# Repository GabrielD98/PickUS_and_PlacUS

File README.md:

# PickUS and PlacUS

A 4-axis (X, Y, Z, Yaw) PCB pick-and-place machine for automated SMD component assembly. Built for the S4 robotics project at Université de Sherbrooke.

## Table of Contents

1. [About](#about)
2. [Features](#features)
3. [Tech Stack](#tech-stack)
4. [Project Structure](#project-structure)
5. [Quick Start](#quick-start)
6. [Roadmap](#roadmap)
7. [Contributing](#contributing)
8. [License](#license)
9. [Contact](#contact)

---

## About

### Problem
Manual SMD component placement onto PCBs is time-consuming and error-prone. Small labs and educational institutions need an affordable pick-and-place machine for fast prototyping.

### Solution
PickUS and PlacUS is an open-source, 4-axis automated pick-and-place machine that:
- Picks SMD components using a vacuum pump system
- Places them onto PCBs with positional accuracy
- Uses stepper motors for precise X, Y, Z, and rotational (Yaw) control
- Integrates with KiCad placement files for automated workflows

### Audience
Ideal for robotics project teams, PCB assembly labs, and makers who need to automate component placement without high capital investment.

---

## Features

- **4-Axis Control**: X, Y, Z positioning + Yaw rotation for flexible placement
- **Vacuum Pick System**: Pneumatic pump and valve for reliable component pickup
- **Pressure Sensing**: Real-time feedback to detect successful component pickup
- **End-Stop Protection**: Z-axis limit switch to prevent collision damage
- **ESP32-S3 Controller**: Over-the-air updateable firmware with multiple I/O options
- **Python HMI**: Cross-platform graphical interface for machine control
- **KiCad Integration**: Direct import of `.pos` placement files for batch production
- **Modular Design**: Separate electrical, firmware, and HMI components

---

## Tech Stack

| Component | Technology |
|-----------|-----------|
| Microcontroller | ESP32-S3 (32-bit, dual-core, 240 MHz) |
| Motor Control | Stepper drivers (NEMA-17 steppers on X,Y,Z and NEMA_8 on YAW) |
| Firmware | C++ with PlatformIO / Arduino framework |
| Motor Library | [AccelStepper](https://github.com/waspinator/AccelStepper) |
| Communication | UART (serial) at 115200 baud |
| HMI | Python 3 + PyQt5/PySimpleGUI |
| Serial Library | `pyserial` |
| PCB Design | KiCad 8+ |
| Schematic | `circuitPNP/` main board + `PCB_test/` test board |

---

## Project Structure

```
PickUS_and_PlacUS/
├── Electrical/              # KiCad schematics and PCB layouts
│   ├── PNP_MOBO_V1/         # Main control board
│   ├── PNP_TEST_CIRCUIT_V1/ # Test board for validation
│   └── README.md            # Electrical recreation guide
├── Firmware_esp32/          # ESP32-S3 firmware (PlatformIO)
│   ├── src/                 # C++ source files
│   ├── lib/                 # Libraries (AccelStepper, etc.)
│   ├── test/                # Unit tests
│   ├── include/             # Header files
│   └── platformio.ini       # PlatformIO config
└── HMI/                     # Python host interface
    ├── src/                 # Main HMI modules
    │   ├── gui/             # GUI components
    │   ├── communication.py # Serial protocol
    │   ├── controller.py    # Command orchestration
    │   ├── main.py          # Entry point
    │   └── ...
    └── tests/               # Unit and integration tests
```

---

## Quick Start

Each subsystem has its own detailed README:

- **[Firmware_esp32/](Firmware_esp32/)** — ESP32-S3 firmware setup and configuration
- **[HMI/](HMI/)** — Python host interface installation and usage
- **[Electrical/](Electrical/)** — PCB design and electrical recreation guide
- **[Mechanical/](Mechanical/)** — Mechanical recreation guide, BOM, and STL

---

## Getting Started

### For Developers

1. Clone this repository
2. Navigate to the subsystem folder of interest (Firmware, HMI, or Electrical)
3. Follow the README in that folder for detailed setup instructions

### Project Overview

| Subsystem | Technology | Purpose |
|-----------|-----------|---------|
| **Firmware_esp32** | C++ with PlatformIO | Real-time motor control, sensor reading, and command execution |
| **HMI** | Python 3 + PyQt5 | Cross-platform UI for machine operation and KiCad file import |
| **Electrical** | KiCad 8+ | Circuit design and PCB layouts |

---

## Roadmap

- [ ] Multi-head support for parallel placement
- [ ] Vision-based component alignment
- [ ] Auto feeder implementation
- [ ] Machine learning for optimal pick order optimization

---

## License

This project uses a split-license model:

- **Software (firmware + HMI source code)**: MIT License ([LICENSE](LICENSE))
- **Hardware design files** (schematics, PCB layouts, fabrication files): CERN Open Hardware Licence v2 - Permissive ([LICENSE-HARDWARE](LICENSE-HARDWARE))

---

## Acknowledgments

- [PlatformIO](https://platformio.org/) for embedded development tools
- [KiCad](https://www.kicad.org/) for PCB design
- [AccelStepper Library](https://www.airspayce.com/mikem/arduino/AccelStepper/) for motor control
- Université de Sherbrooke robotics program
- All contributors and testers

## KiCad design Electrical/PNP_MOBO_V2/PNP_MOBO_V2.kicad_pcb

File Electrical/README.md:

# Electrical Guide

PCB design and schematics for the PickUS and PlacUS machine. Includes main control board and test board for validation.

## Scope

The electrical work is split into two KiCad projects:

- `PNP_MOBO_V1/` — Main control board for the machine
- `PNP_TEST_CIRCUIT_V1/` — Test board for validating pick and place operation

## Prerequisites

- KiCad 8 (recommended)
- Basic soldering tools and bench power supply for bring-up
- Optional for production:
  - PCB manufacturer account (JLCPCB, PCBWay, etc.)
  - Assembly service for SMT components

---

## Installation & Setup

1. **Install KiCad**
   - Download from [https://www.kicad.org/](https://www.kicad.org/)
   - Install version 8 or later

2. **Open a project**
   ```bash
   cd Electrical/circuitPNP
   ```
   Or for the test board:
   ```bash
   cd Electrical/PCB_test
   ```

3. **Open in KiCad**
   - Double-click the `.kicad_pro` file, or
   - Launch KiCad and open the project file

---

## Project Structure

```
Electrical/
├── PNP_MOBO_V1/
│   ├── PNP_MOBO_V1.kicad_sch      # Main board schematic
│   ├── PNP_MOBO_V1.kicad_pcb      # Main board PCB layout
│   ├── PNP_MOBO_V1.kicad_pro      # Project file
│   ├── fabricationFile.zip       # Gerber, drill, and BOM exports
│   └── bom/                      # Bill of materials
├── PNP_TEST_CIRCUIT_V1/
|   ├── STENCIL.3mf
│   ├── PNP_TEST_CIRCUIT_V1.kicad_sch        # Test board schematic
│   ├── PNP_TEST_CIRCUIT_V1.kicad_pcb        # Test board PCB layout
│   └── PNP_TEST_CIRCUIT_V1.kicad_pro        # Project file
└── README.md
```

---

## Main Board (`PNP_MOBO_V1`)

### Key Subsystems

- **ESP32 Control & Communication**: Control and USB serial lines
- **Stepper Driver Interfaces**: DIR/STEP/EN signals for X, Y, Z, YAW motors
- **Vacuum Pump & Valve Switching**: Power control for pickup system
- **Pressure Sensor Interface**: Two-wire clock+data interface (bit-banged): toggle clock, sensor outputs one data bit per pulse (used for grip detection)
- **End-Stop Connectors**: Limit switch inputs for X, Y, Z axes
- **Can/I2C Connectors**: Additional expansion headers

---

## Test Board (`PNP_TEST_CIRCUIT_V1`)

### Purpose

Validate the pick-and-place workflow with a dedicated test board featuring standard footprints.

---

## Bring-Up & Validation

Complete this checklist as you recreate each board:

- [ ] KiCad project opens without missing symbol/footprint errors
- [ ] ERC passes with no critical errors
- [ ] All connectors have clear pin naming in schematic and silkscreen
- [ ] DRC passes with no critical errors
- [ ] Gerber and drill files exported
- [ ] BOM exported and validated with available stock
- [ ] Board assembled and visually inspected
- [ ] Continuity test completed on power rails and critical nets
- [ ] First power-on done with current-limited supply (no shorts)
- [ ] ESP32 and peripherals communication validated via firmware
- [ ] Motors, pump/valve, and sensors verified functionally

---

## Versioning & Release

- Use a version tag in the board title block and filenames (e.g., `v1`, `v2`)
- Commit schematic and PCB changes together

---

## BOM Organization

Recommended workflow:

- **PCB parts:** use the KiCad interactive BOM export (`PNP_MOBO_V1/bom/ibom.html`)
- **All non-PCB parts (electrical + mechanical):** see [Mechanical BOM](../Mechanical)

## Fabrication Tools

- **For stencil generation:** we use [gerber_to_scad](https://github.com/kirberich/gerber_to_scad)
- **Purpose:** generate stencil or fabrication geometry from the PCB source files

---

## Troubleshooting

### Missing Symbols or Footprints
- Verify all library paths are configured in KiCad
- Check that custom symbols/footprints are in the project library directory

### ERC or DRC Errors
- Review each error and determine if it's a genuine violation or a false positive
- Suppress false positives only after verification

### Design Rule Violations
- Consult your PCB manufacturer's design rules for clearance, trace width, and via sizes
- Update KiCad design rules to match your manufacturer specifications

---

## Next Steps

- See [main README](../README.md) for project overview
- See [Firmware README](../Firmware_esp32/) for ESP32 setup and firmware details
- See [HMI README](../HMI/) for host interface setup
- See [Mechanical README](../Mechanical/) for mechanical design

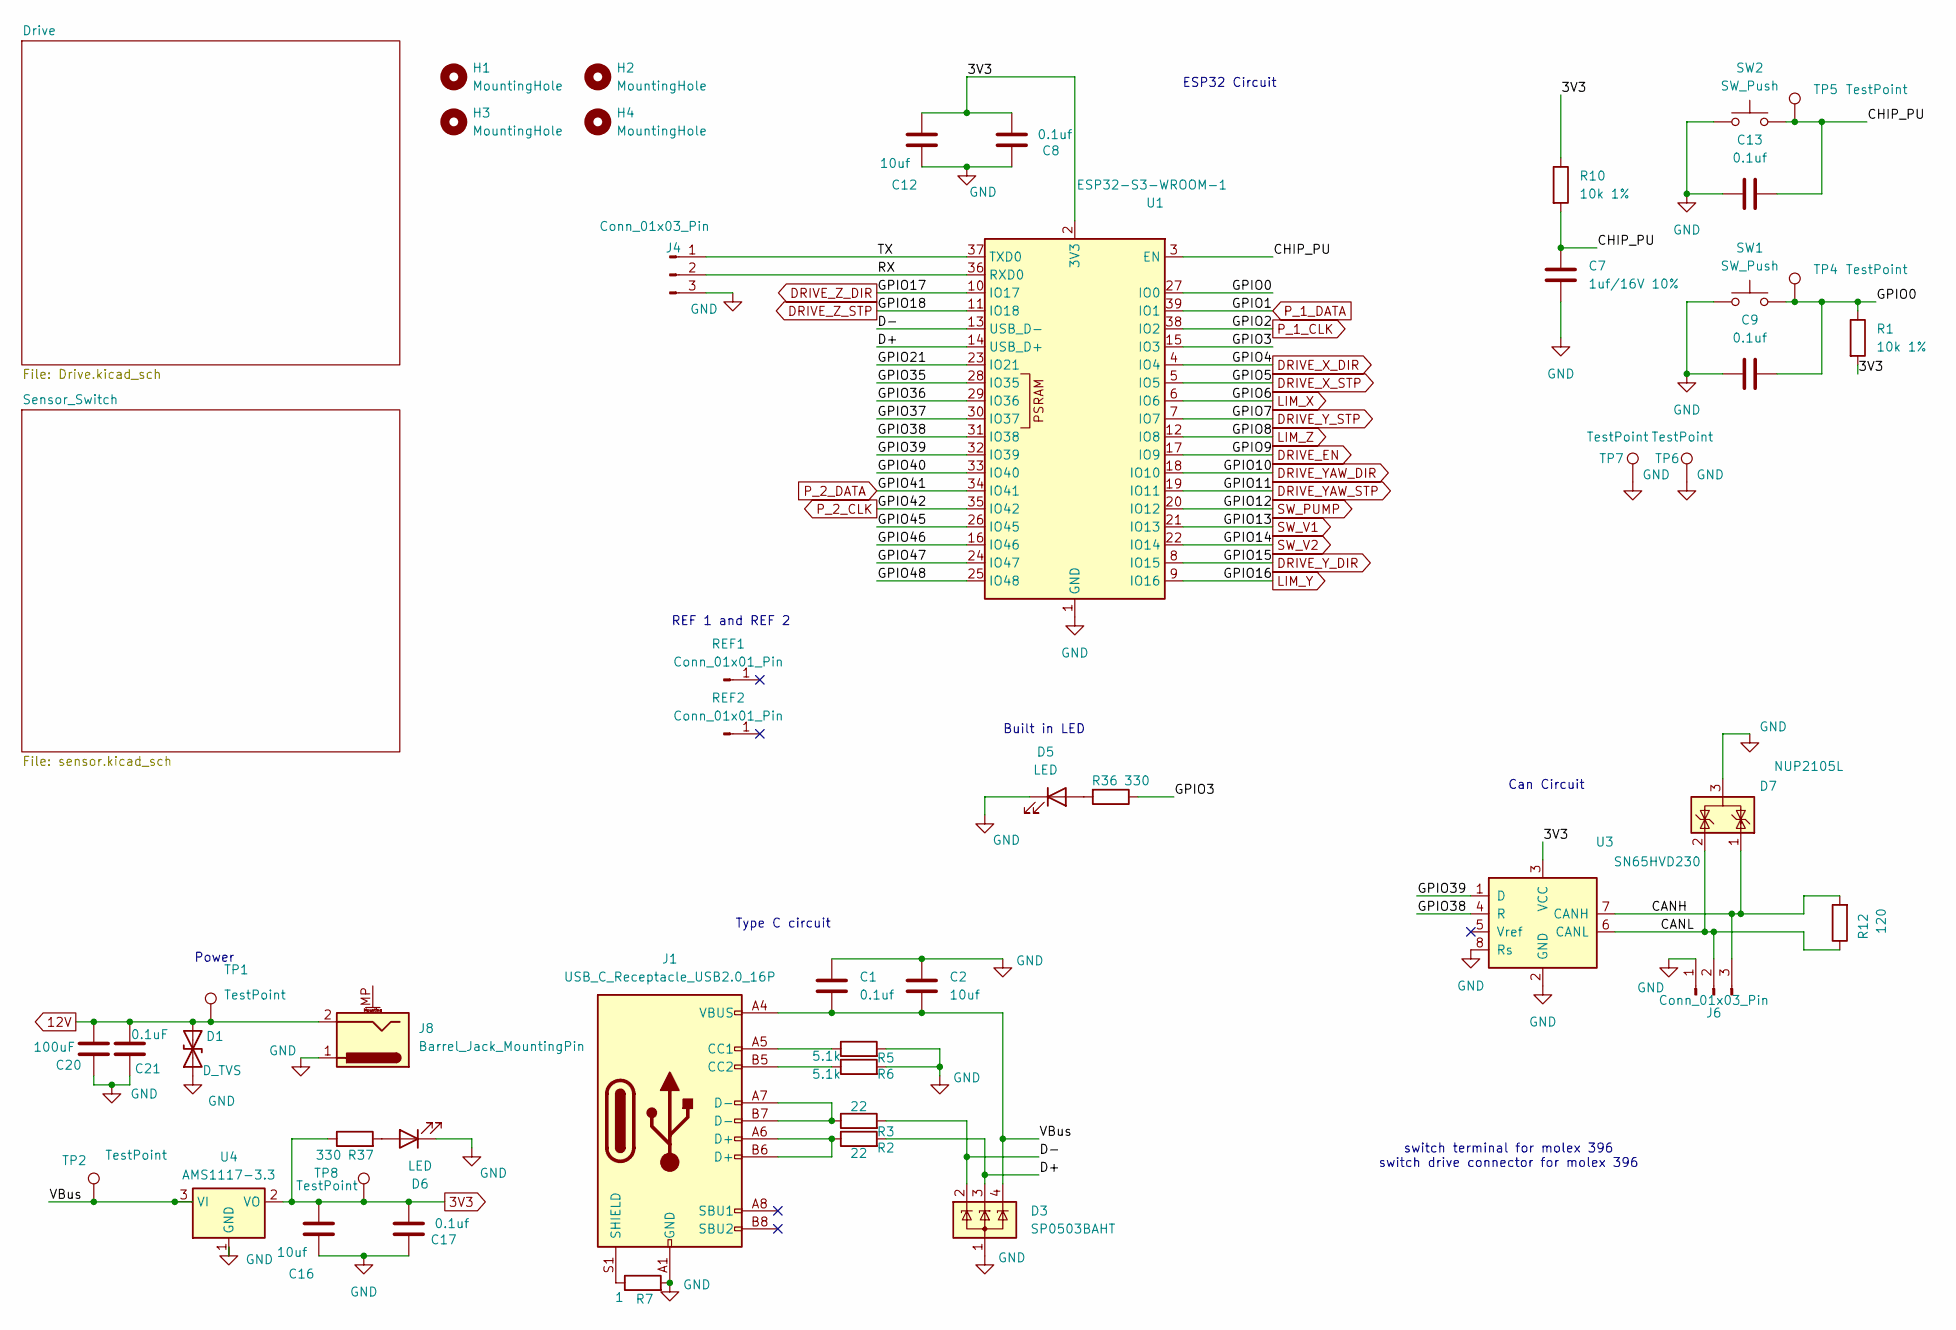
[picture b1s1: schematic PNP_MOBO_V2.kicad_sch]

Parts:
C1, C8, C9, C13, C17: 0.1uf; C_0603_1608Metric_Pad1.08x0.95mm_HandSolder
C2, C12, C16: 10uf; C_0603_1608Metric_Pad1.08x0.95mm_HandSolder
C7: 1uf/16V 10%; C_0603_1608Metric_Pad1.08x0.95mm_HandSolder
C20: 100uF; CP_Elec_8x10
C21: 0.1uF; C_0603_1608Metric_Pad1.08x0.95mm_HandSolder
D1: D_TVS; D_SMB
D3: SP0503BAHT; SOT-143
D5, D6: LED; LED_0603_1608Metric
D7: NUP2105L; SOT-23
H1, H2, H3, H4: MountingHole; MountingHole_3.2mm_M3
J1: USB_C_Receptacle_USB2.0_16P; USB_C_Receptacle_GCT_USB4105-xx-A_16P_TopMnt_Horizontal
J4: Conn_01x03_Pin; PinHeader_1x03_P2.54mm_Vertical
J6: Conn_01x03_Pin; Molex_KK-254_AE-6410-03A_1x03_P2.54mm_Vertical
J8: Barrel_Jack_MountingPin; BarrelJack_CUI_PJ-063AH_Horizontal
R1, R10: 10k 1%; R_0603_1608Metric_Pad0.98x0.95mm_HandSolder
R2, R3: 22; R_0603_1608Metric_Pad0.98x0.95mm_HandSolder
R5, R6: 5.1k; R_0603_1608Metric_Pad0.98x0.95mm_HandSolder
R7: 1; R_0603_1608Metric_Pad0.98x0.95mm_HandSolder
R12: 120; R_0603_1608Metric_Pad0.98x0.95mm_HandSolder
R36, R37: 330; R_0603_1608Metric_Pad0.98x0.95mm_HandSolder
REF1, REF2: Conn_01x01_Pin; PinHeader_1x01_P1.00mm_Vertical
SW1, SW2: SW_Push; SW_SPST_PTS647_Sx38
TP1, TP2, TP4, TP5, TP6, TP7, TP8: TestPoint; TestPoint_Pad_D2.0mm
U1: ESP32-S3-WROOM-1
U3: SN65HVD230; SOIC-8_3.9x4.9mm_P1.27mm
U4: AMS1117-3.3; SOT-223-3_TabPin2

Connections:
3V3: C8.2, C12.2, C16.2, C17.2, R1.2, R10.1, R37.1, TP8.1, U1.2 (3V3), U3.3 (VCC), U4.2 (VO); also elsewhere on the board
12V: C20.1, C21.1, D1.2 (A2), J8.2, TP1.1; also elsewhere on the board
/CANH: D7.1 (K), J6.3, R12.2, U3.7 (CANH)
/CANL: D7.2 (K), J6.2, R12.1, U3.6 (CANL)
/CHIP_PU: C7.1, C13.1, R10.2, SW2.2, TP5.1, U1.3 (EN)
/D+: D3.3 (K), R2.2, U1.14 (USB_D+)
/D-: D3.2 (K), R3.2, U1.13 (USB_D-)
/GPIO0: C9.1, R1.1, SW1.2, TP4.1, U1.27 (IO0)
/GPIO3: R36.1, U1.15 (IO3)
/GPIO21: U1.23 (IO21)
/GPIO35: U1.28 (IO35)
/GPIO36: U1.29 (IO36)
/GPIO37: U1.30 (IO37)
/GPIO38: U1.31 (IO38), U3.4 (R)
/GPIO39: U1.32 (IO39), U3.1 (D)
/GPIO40: U1.33 (IO40)
/GPIO45: U1.26 (IO45)
/GPIO46: U1.16 (IO46)
/GPIO47: U1.24 (IO47)
/GPIO48: U1.25 (IO48)
/RX: J4.2, U1.36 (RXD0)
/TX: J4.1, U1.37 (TXD0)
/VBus: C1.2, C2.2, D3.4 (K), J1.A4 (VBUS), J1.A9 (VBUS), J1.B4 (VBUS), J1.B9 (VBUS), TP2.1, U4.3 (VI)
DRIVE_EN: U1.17 (IO9); also elsewhere on the board
DRIVE_X_DIR: U1.4 (IO4); also elsewhere on the board
DRIVE_X_STP: U1.5 (IO5); also elsewhere on the board
DRIVE_YAW_DIR: U1.18 (IO10); also elsewhere on the board
DRIVE_YAW_STP: U1.19 (IO11); also elsewhere on the board
DRIVE_Y_DIR: U1.8 (IO15); also elsewhere on the board
DRIVE_Y_STP: U1.7 (IO7); also elsewhere on the board
DRIVE_Z_DIR: U1.10 (IO17); also elsewhere on the board
DRIVE_Z_STP: U1.11 (IO18); also elsewhere on the board
GND: C1.1, C2.1, C7.2, C8.1, C9.2, C12.1, C13.2, C16.1, C17.1, C20.2, C21.2, D1.1 (A1), D3.1 (A), D5.1 (K), D6.1 (K), D7.3 (A), J1.A1 (GND), J1.A12 (GND), J1.B1 (GND), J1.B12 (GND), J4.3, J6.1, J8.1, R5.2, R6.2, R7.2, SW1.1, SW2.1, TP6.1, TP7.1, U1.1 (GND), U1.40 (GND), U1.41 (GND), U3.2 (GND), U3.8 (Rs), U4.1 (GND); also elsewhere on the board
LIM_X: U1.6 (IO6); also elsewhere on the board
LIM_Y: U1.9 (IO16); also elsewhere on the board
LIM_Z: U1.12 (IO8); also elsewhere on the board
unnamed: D5.2 (A), R36.2
unnamed: D6.2 (A), R37.2
unnamed: J1.A5 (CC1), R5.1
unnamed: J1.B5 (CC2), R6.1
unnamed: J1.A6 (D+), J1.B6 (D+), R2.1
unnamed: J1.A7 (D-), J1.B7 (D-), R3.1
unnamed: J1.S1 (SHIELD), R7.1
P_1_CLK: U1.38 (IO2); also elsewhere on the board
P_1_DATA: U1.39 (IO1); also elsewhere on the board
P_2_CLK: U1.35 (IO42); also elsewhere on the board
P_2_DATA: U1.34 (IO41); also elsewhere on the board
SW_PUMP: U1.20 (IO12); also elsewhere on the board
SW_V1: U1.21 (IO13); also elsewhere on the board
SW_V2: U1.22 (IO14); also elsewhere on the board

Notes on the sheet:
Built in LED
Type C circuit
Can Circuit
Power
REF 1 and REF 2
ESP32 Circuit
switch terminal for molex 396 switch drive connector for molex 396

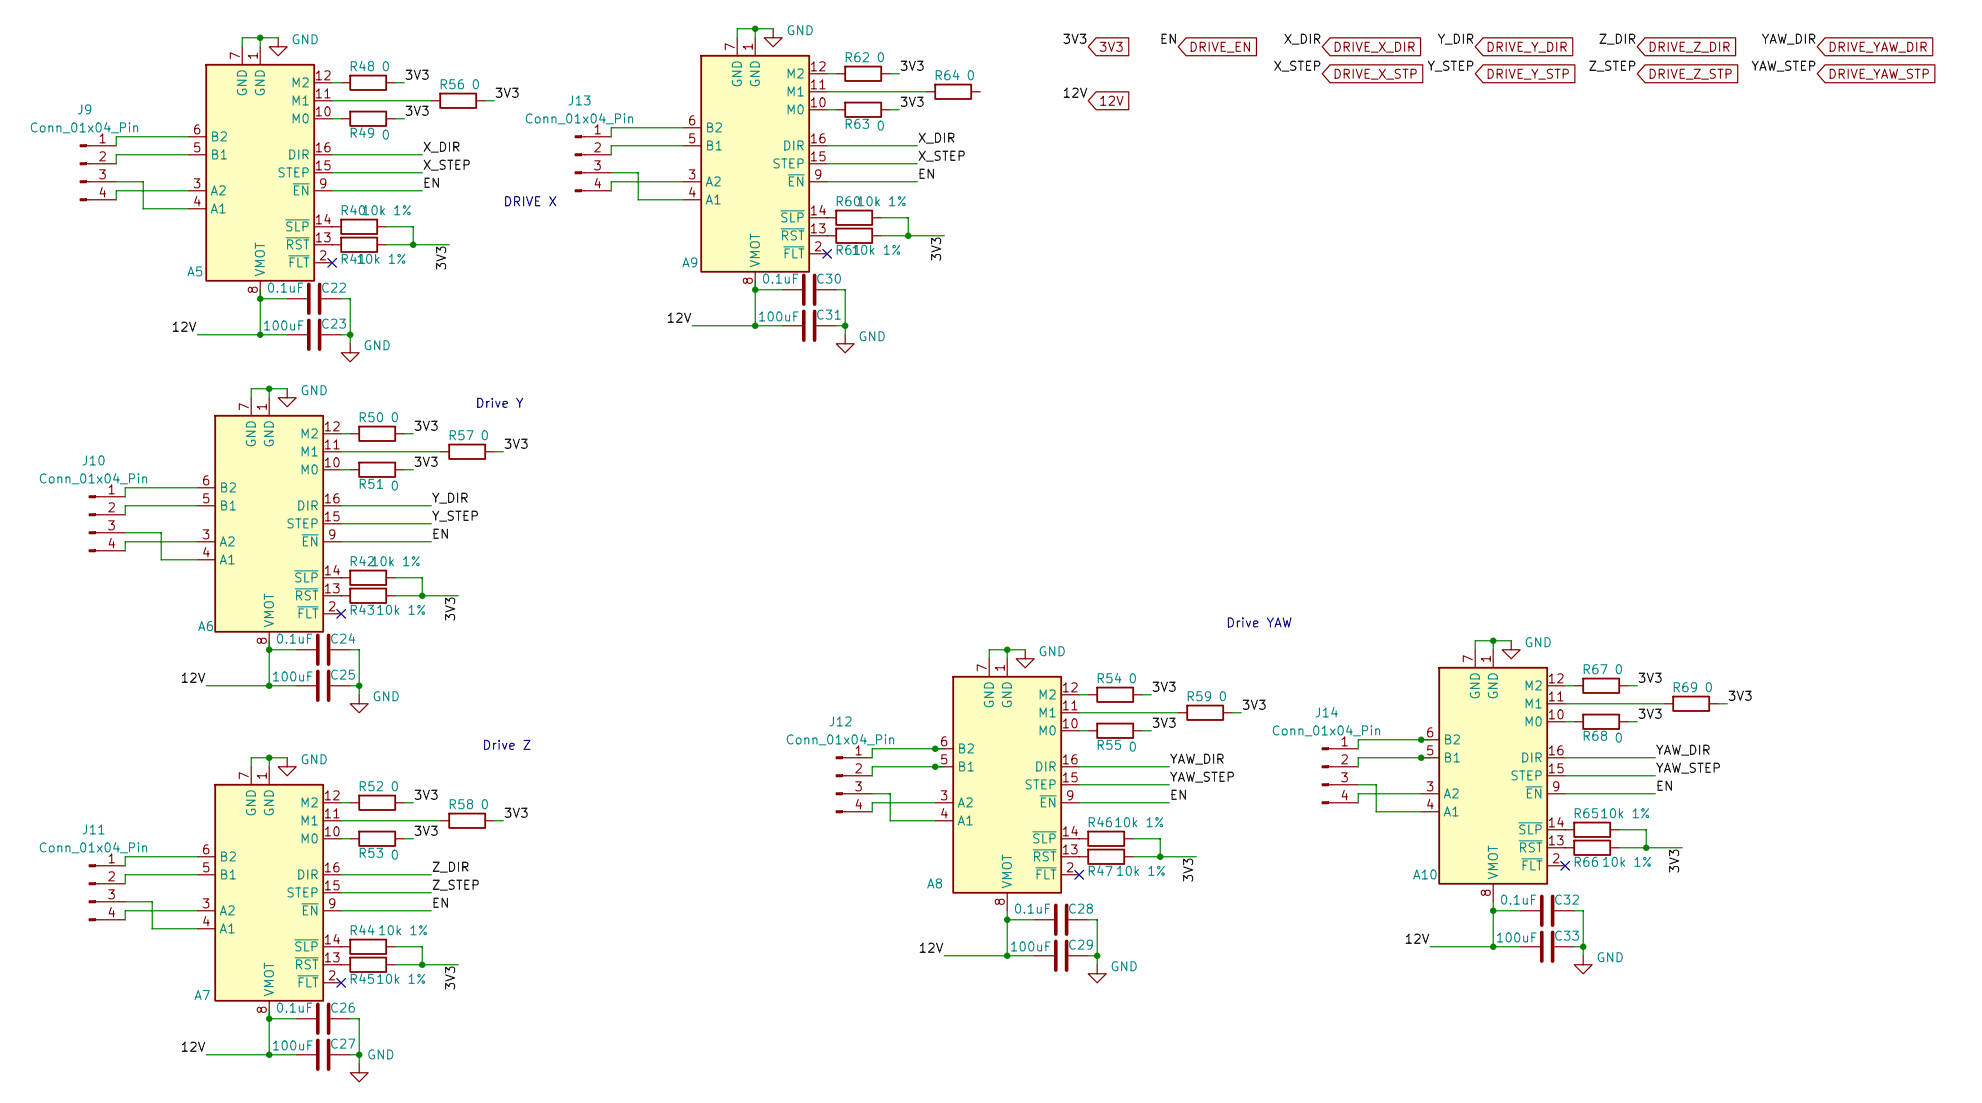
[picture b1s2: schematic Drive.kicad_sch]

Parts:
A5, A6, A7, A8, A9, A10: Pololu_Breakout_DRV8825; Pololu_Breakout-16_15.2x20.3mm
C22, C24, C26, C28, C30, C32: 0.1uF; C_0603_1608Metric_Pad1.08x0.95mm_HandSolder
C23, C25, C27, C29, C31, C33: 100uF; CP_Elec_8x10
J9, J10, J11, J12, J13, J14: Conn_01x04_Pin; JST_XH_B4B-XH-A_1x04_P2.50mm_Vertical
R40, R41, R42, R43, R44, R45, R46, R47, R60, R61, R65, R66: 10k 1%; R_0603_1608Metric_Pad0.98x0.95mm_HandSolder
R48, R49, R50, R51, R52, R53, R54, R55, R56, R57, R58, R59, R62, R63, R64, R67, R68, R69: 0; R_0402_1005Metric

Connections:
3V3: R40.1, R41.1, R42.1, R43.1, R44.1, R45.1, R46.1, R47.1, R48.1, R49.1, R50.1, R51.1, R52.1, R53.1, R54.1, R55.1, R56.1, R57.1, R58.1, R59.1, R60.1, R61.1, R62.1, R63.1, R65.1, R66.1, R67.1, R68.1, R69.1; also elsewhere on the board
12V: A5.8 (VMOT), A6.8 (VMOT), A7.8 (VMOT), A8.8 (VMOT), A9.8 (VMOT), A10.8 (VMOT), C22.1, C23.1, C24.1, C25.1, C26.1, C27.1, C28.1, C29.1, C30.1, C31.1, C32.1, C33.1; also elsewhere on the board
DRIVE_EN: A5.9 (~EN), A6.9 (~EN), A7.9 (~EN), A8.9 (~EN), A9.9 (~EN), A10.9 (~EN); also elsewhere on the board
DRIVE_X_DIR: A5.16 (DIR), A9.16 (DIR); also elsewhere on the board
DRIVE_X_STP: A5.15 (STEP), A9.15 (STEP); also elsewhere on the board
DRIVE_YAW_DIR: A8.16 (DIR), A10.16 (DIR); also elsewhere on the board
DRIVE_YAW_STP: A8.15 (STEP), A10.15 (STEP); also elsewhere on the board
DRIVE_Y_DIR: A6.16 (DIR); also elsewhere on the board
DRIVE_Y_STP: A6.15 (STEP); also elsewhere on the board
DRIVE_Z_DIR: A7.16 (DIR); also elsewhere on the board
DRIVE_Z_STP: A7.15 (STEP); also elsewhere on the board
GND: A5.1 (GND), A5.7 (GND), A6.1 (GND), A6.7 (GND), A7.1 (GND), A7.7 (GND), A8.1 (GND), A8.7 (GND), A9.1 (GND), A9.7 (GND), A10.1 (GND), A10.7 (GND), C22.2, C23.2, C24.2, C25.2, C26.2, C27.2, C28.2, C29.2, C30.2, C31.2, C32.2, C33.2; also elsewhere on the board
unnamed: A5.4 (A1), J9.3
unnamed: A5.3 (A2), J9.4
unnamed: A5.5 (B1), J9.2
unnamed: A5.6 (B2), J9.1
unnamed: A5.10 (M0), R49.2
unnamed: A5.11 (M1), R56.2
unnamed: A5.12 (M2), R48.2
unnamed: A5.13 (~RST), R41.2
unnamed: A5.14 (~SLP), R40.2
unnamed: A6.4 (A1), J10.3
unnamed: A6.3 (A2), J10.4
unnamed: A6.5 (B1), J10.2
unnamed: A6.6 (B2), J10.1
unnamed: A6.10 (M0), R51.2
unnamed: A6.11 (M1), R57.2
unnamed: A6.12 (M2), R50.2
unnamed: A6.13 (~RST), R43.2
unnamed: A6.14 (~SLP), R42.2
unnamed: A7.4 (A1), J11.3
unnamed: A7.3 (A2), J11.4
unnamed: A7.5 (B1), J11.2
unnamed: A7.6 (B2), J11.1
unnamed: A7.10 (M0), R53.2
unnamed: A7.11 (M1), R58.2
unnamed: A7.12 (M2), R52.2
unnamed: A7.13 (~RST), R45.2
unnamed: A7.14 (~SLP), R44.2
unnamed: A8.4 (A1), J12.3
unnamed: A8.3 (A2), J12.4
unnamed: A8.5 (B1), J12.2
unnamed: A8.6 (B2), J12.1
unnamed: A8.10 (M0), R55.2
unnamed: A8.11 (M1), R59.2
unnamed: A8.12 (M2), R54.2
unnamed: A8.13 (~RST), R47.2
unnamed: A8.14 (~SLP), R46.2
unnamed: A9.4 (A1), J13.3
unnamed: A9.3 (A2), J13.4
unnamed: A9.5 (B1), J13.2
unnamed: A9.6 (B2), J13.1
unnamed: A9.10 (M0), R63.2
unnamed: A9.11 (M1), R64.2
unnamed: A9.12 (M2), R62.2
unnamed: A9.13 (~RST), R61.2
unnamed: A9.14 (~SLP), R60.2
unnamed: A10.4 (A1), J14.3
unnamed: A10.3 (A2), J14.4
unnamed: A10.5 (B1), J14.2
unnamed: A10.6 (B2), J14.1
unnamed: A10.10 (M0), R68.2
unnamed: A10.11 (M1), R69.2
unnamed: A10.12 (M2), R67.2
unnamed: A10.13 (~RST), R66.2
unnamed: A10.14 (~SLP), R65.2

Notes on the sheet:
Drive Z
DRIVE X
Drive YAW
Drive Y

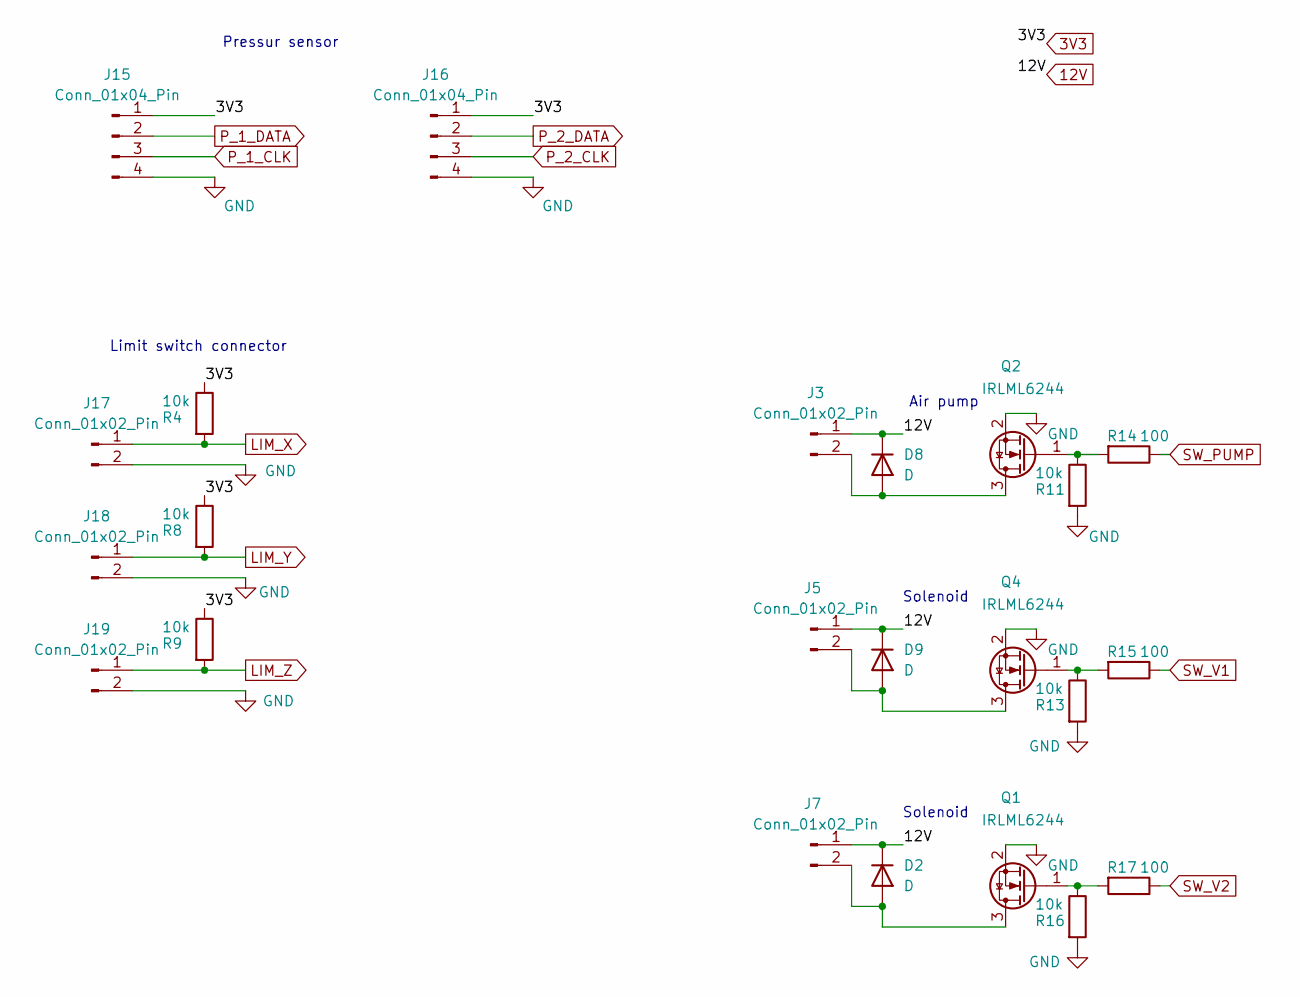
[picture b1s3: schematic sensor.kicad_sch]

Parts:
D2, D8, D9: D; D_SMB
J3, J5, J7, J17, J18, J19: Conn_01x02_Pin; Molex_KK-254_AE-6410-02A_1x02_P2.54mm_Vertical
J15, J16: Conn_01x04_Pin; PinSocket_1x04_P2.54mm_Vertical
Q1, Q2, Q4: IRLML6244; SOT-23
R4, R8, R9, R11, R13, R16: 10k; R_0603_1608Metric_Pad0.98x0.95mm_HandSolder
R14, R15, R17: 100; R_0603_1608Metric_Pad0.98x0.95mm_HandSolder

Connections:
3V3: J15.1, J16.1, R4.1, R8.1, R9.1; also elsewhere on the board
12V: D2.1 (K), D8.1 (K), D9.1 (K), J3.1, J5.1, J7.1; also elsewhere on the board
GND: J15.4, J16.4, J17.2, J18.2, J19.2, Q1.2 (S), Q2.2 (S), Q4.2 (S), R11.2, R13.2, R16.2; also elsewhere on the board
LIM_X: J17.1, R4.2; also elsewhere on the board
LIM_Y: J18.1, R8.2; also elsewhere on the board
LIM_Z: J19.1, R9.2; also elsewhere on the board
unnamed: D2.2 (A), J7.2, Q1.3 (D)
unnamed: D8.2 (A), J3.2, Q2.3 (D)
unnamed: D9.2 (A), J5.2, Q4.3 (D)
unnamed: Q1.1 (G), R16.1, R17.2
unnamed: Q2.1 (G), R11.1, R14.2
unnamed: Q4.1 (G), R13.1, R15.2
P_1_CLK: J15.3; also elsewhere on the board
P_1_DATA: J15.2; also elsewhere on the board
P_2_CLK: J16.3; also elsewhere on the board
P_2_DATA: J16.2; also elsewhere on the board
SW_PUMP: R14.1; also elsewhere on the board
SW_V1: R15.1; also elsewhere on the board
SW_V2: R17.1; also elsewhere on the board

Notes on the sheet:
Solenoid
Air pump
Limit switch connector
Pressur sensor

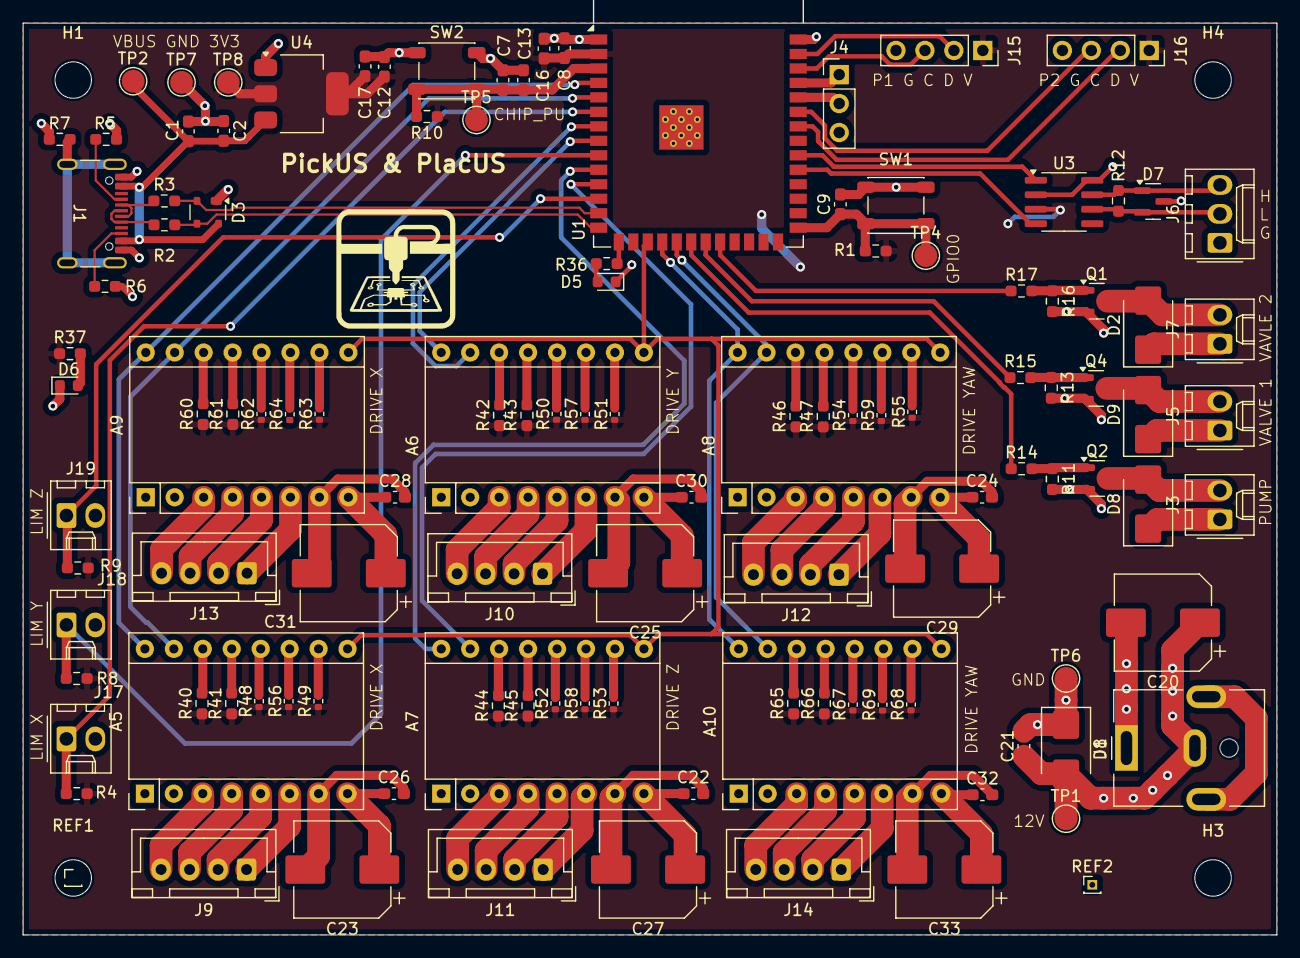
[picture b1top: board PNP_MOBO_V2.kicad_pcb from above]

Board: 4 copper layers, 110.0 x 80.0 mm, 125 parts (0 on the bottom side), 101 nets.

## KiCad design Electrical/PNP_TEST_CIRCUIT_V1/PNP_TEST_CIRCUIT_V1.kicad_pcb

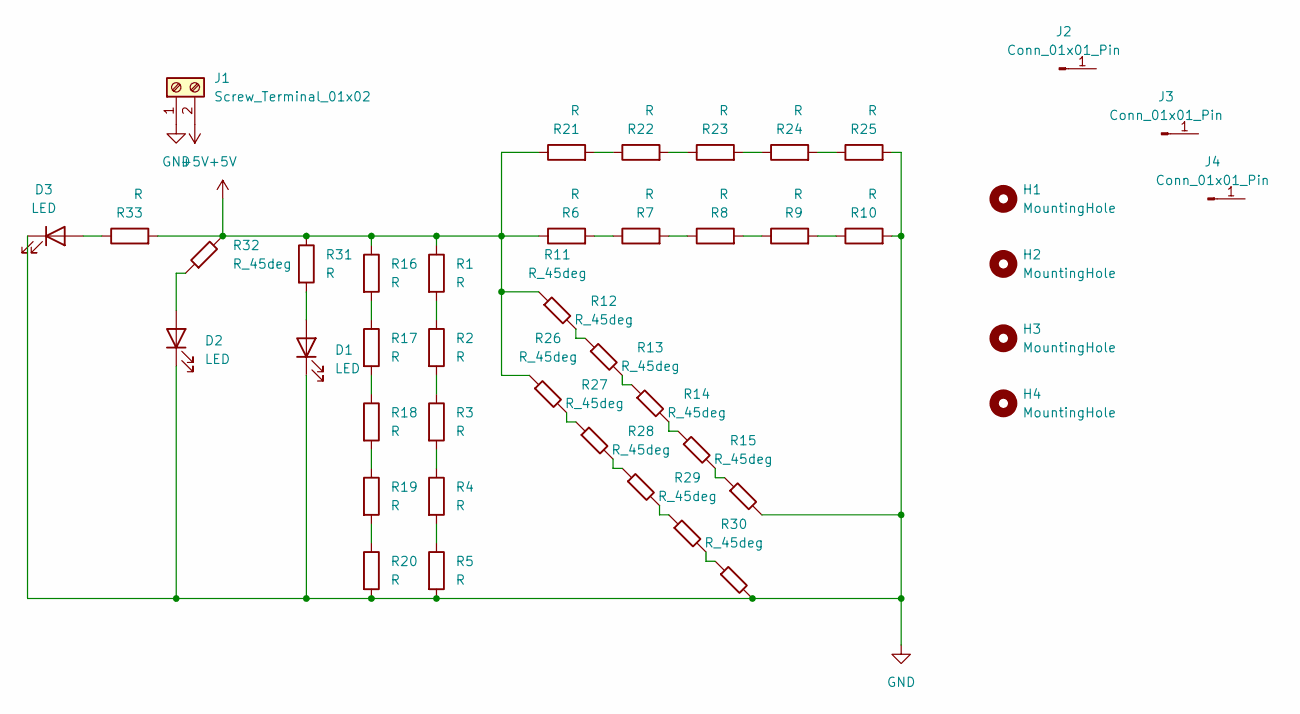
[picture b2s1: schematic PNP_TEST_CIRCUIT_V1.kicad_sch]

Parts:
D1, D2, D3: LED; LED_0805_2012Metric
H1, H2, H3, H4: MountingHole; MountingHole_3.2mm_M3
J1: Screw_Terminal_01x02; Molex_KK-396_A-41792-0002_1x02_P3.96mm_Horizontal
J2, J3, J4: Conn_01x01_Pin; PinHeader_1x01_P1.00mm_Vertical
R1, R2, R3, R4, R5, R6, R7, R8, R9, R10, R31, R33: R; R_0805_2012Metric
R11, R12, R13, R14, R15, R32: R_45deg; R_0805_2012Metric
R16, R17, R18, R19, R20, R21, R22, R23, R24, R25: R; R_0603_1608Metric
R26, R27, R28, R29, R30: R_45deg; R_0603_1608Metric

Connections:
+5V: J1.2, R1.1, R6.1, R11.1, R16.1, R21.1, R26.1, R31.1, R32.2, R33.2
GND: D1.1 (K), D2.1 (K), D3.1 (K), J1.1, R5.2, R10.2, R15.2, R20.2, R25.2, R30.2
unnamed: D1.2 (A), R31.2
unnamed: D2.2 (A), R32.1
unnamed: D3.2 (A), R33.1
unnamed: R1.2, R2.1
unnamed: R2.2, R3.1
unnamed: R3.2, R4.1
unnamed: R4.2, R5.1
unnamed: R6.2, R7.1
unnamed: R7.2, R8.1
unnamed: R8.2, R9.1
unnamed: R9.2, R10.1
unnamed: R11.2, R12.1
unnamed: R12.2, R13.1
unnamed: R13.2, R14.1
unnamed: R14.2, R15.1
unnamed: R16.2, R17.1
unnamed: R17.2, R18.1
unnamed: R18.2, R19.1
unnamed: R19.2, R20.1
unnamed: R21.2, R22.1
unnamed: R22.2, R23.1
unnamed: R23.2, R24.1
unnamed: R24.2, R25.1
unnamed: R26.2, R27.1
unnamed: R27.2, R28.1
unnamed: R28.2, R29.1
unnamed: R29.2, R30.1

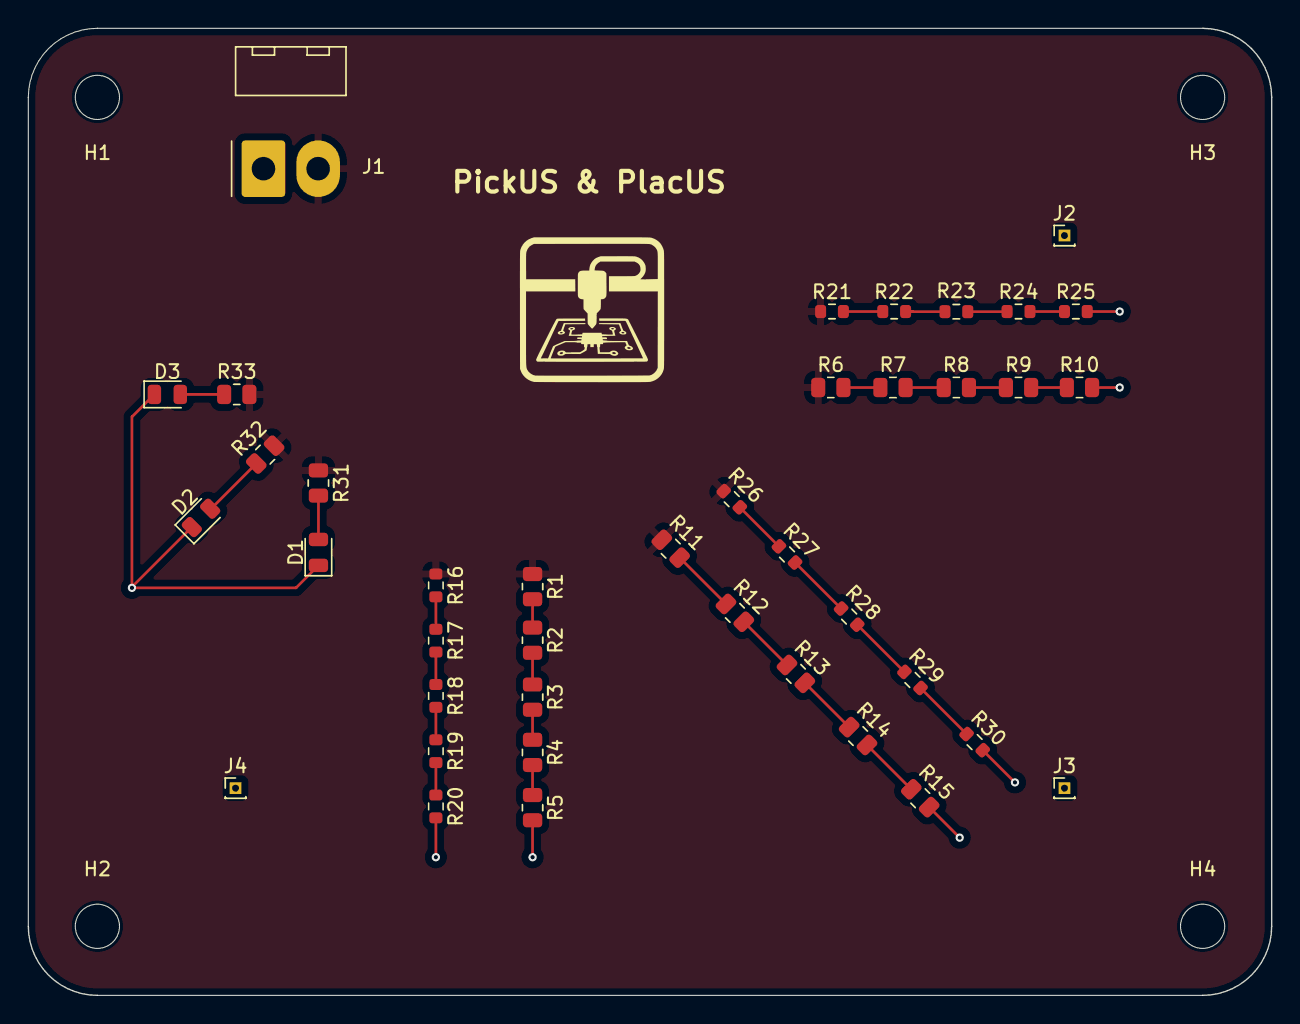
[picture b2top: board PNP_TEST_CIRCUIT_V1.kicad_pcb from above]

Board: 2 copper layers, 90.0 x 70.0 mm, 44 parts (0 on the bottom side), 29 nets.
